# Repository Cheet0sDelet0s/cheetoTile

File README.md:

# cheetoTile
an attiny based rgb led tiling system

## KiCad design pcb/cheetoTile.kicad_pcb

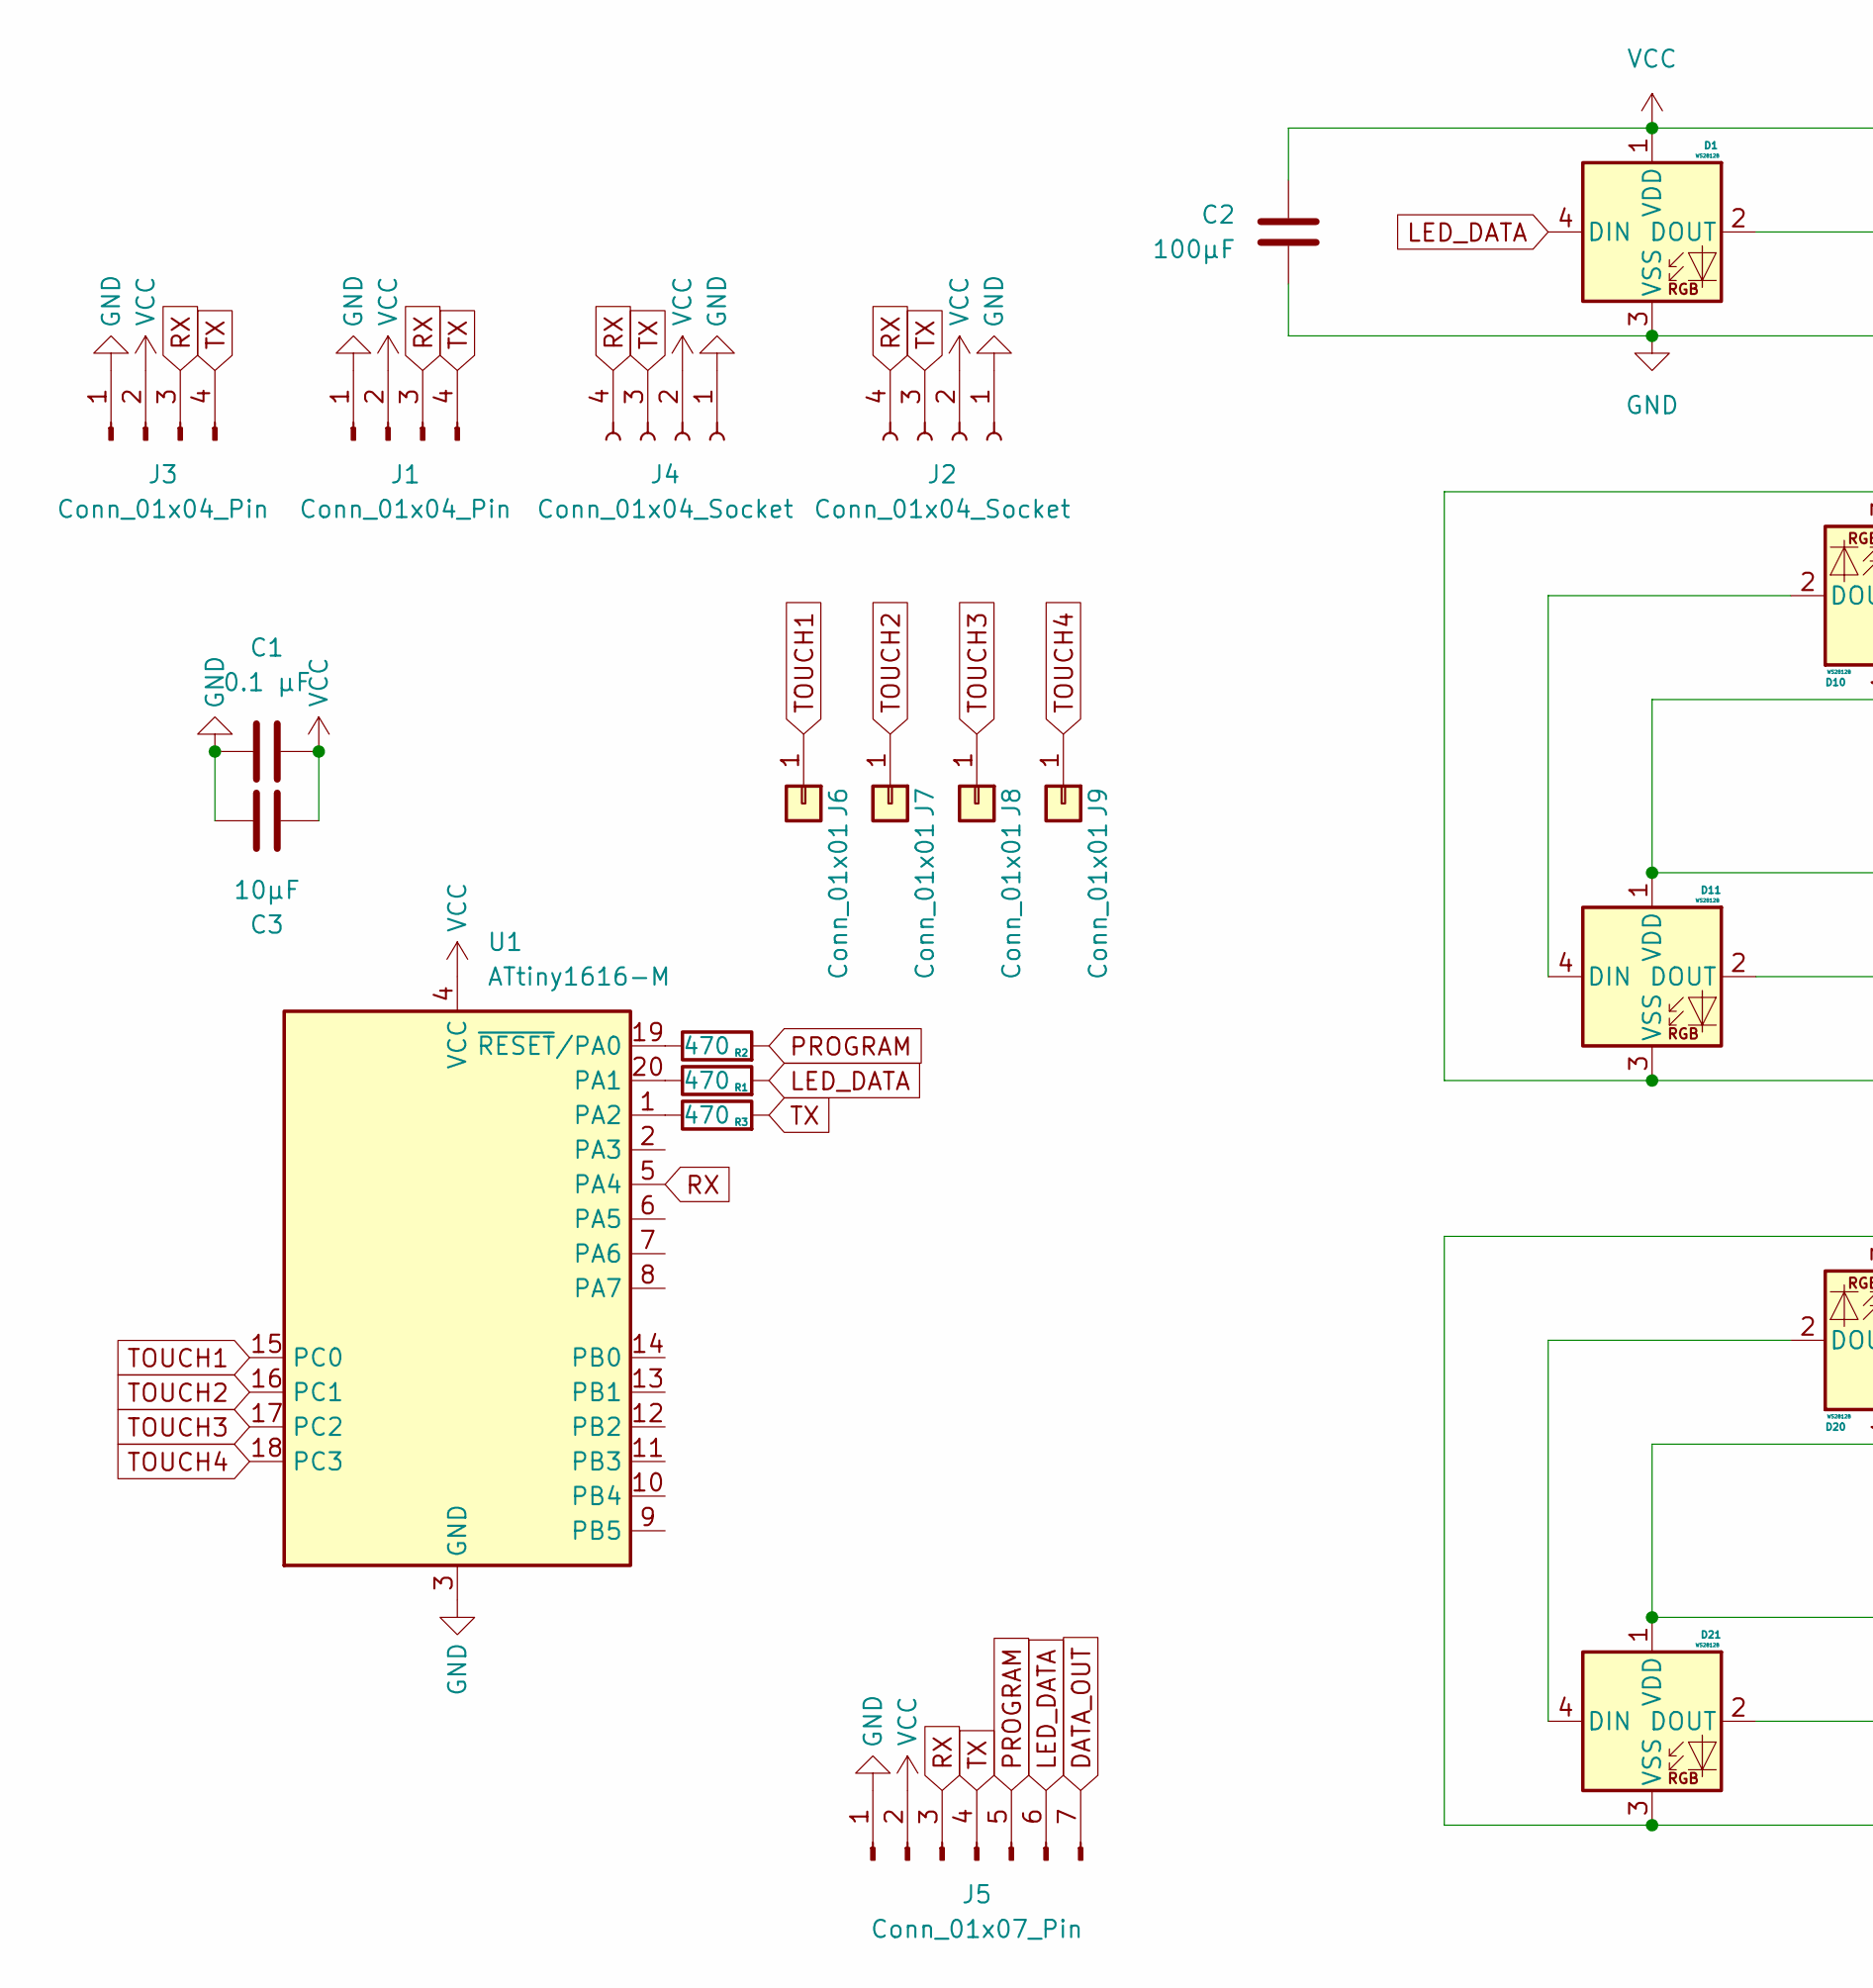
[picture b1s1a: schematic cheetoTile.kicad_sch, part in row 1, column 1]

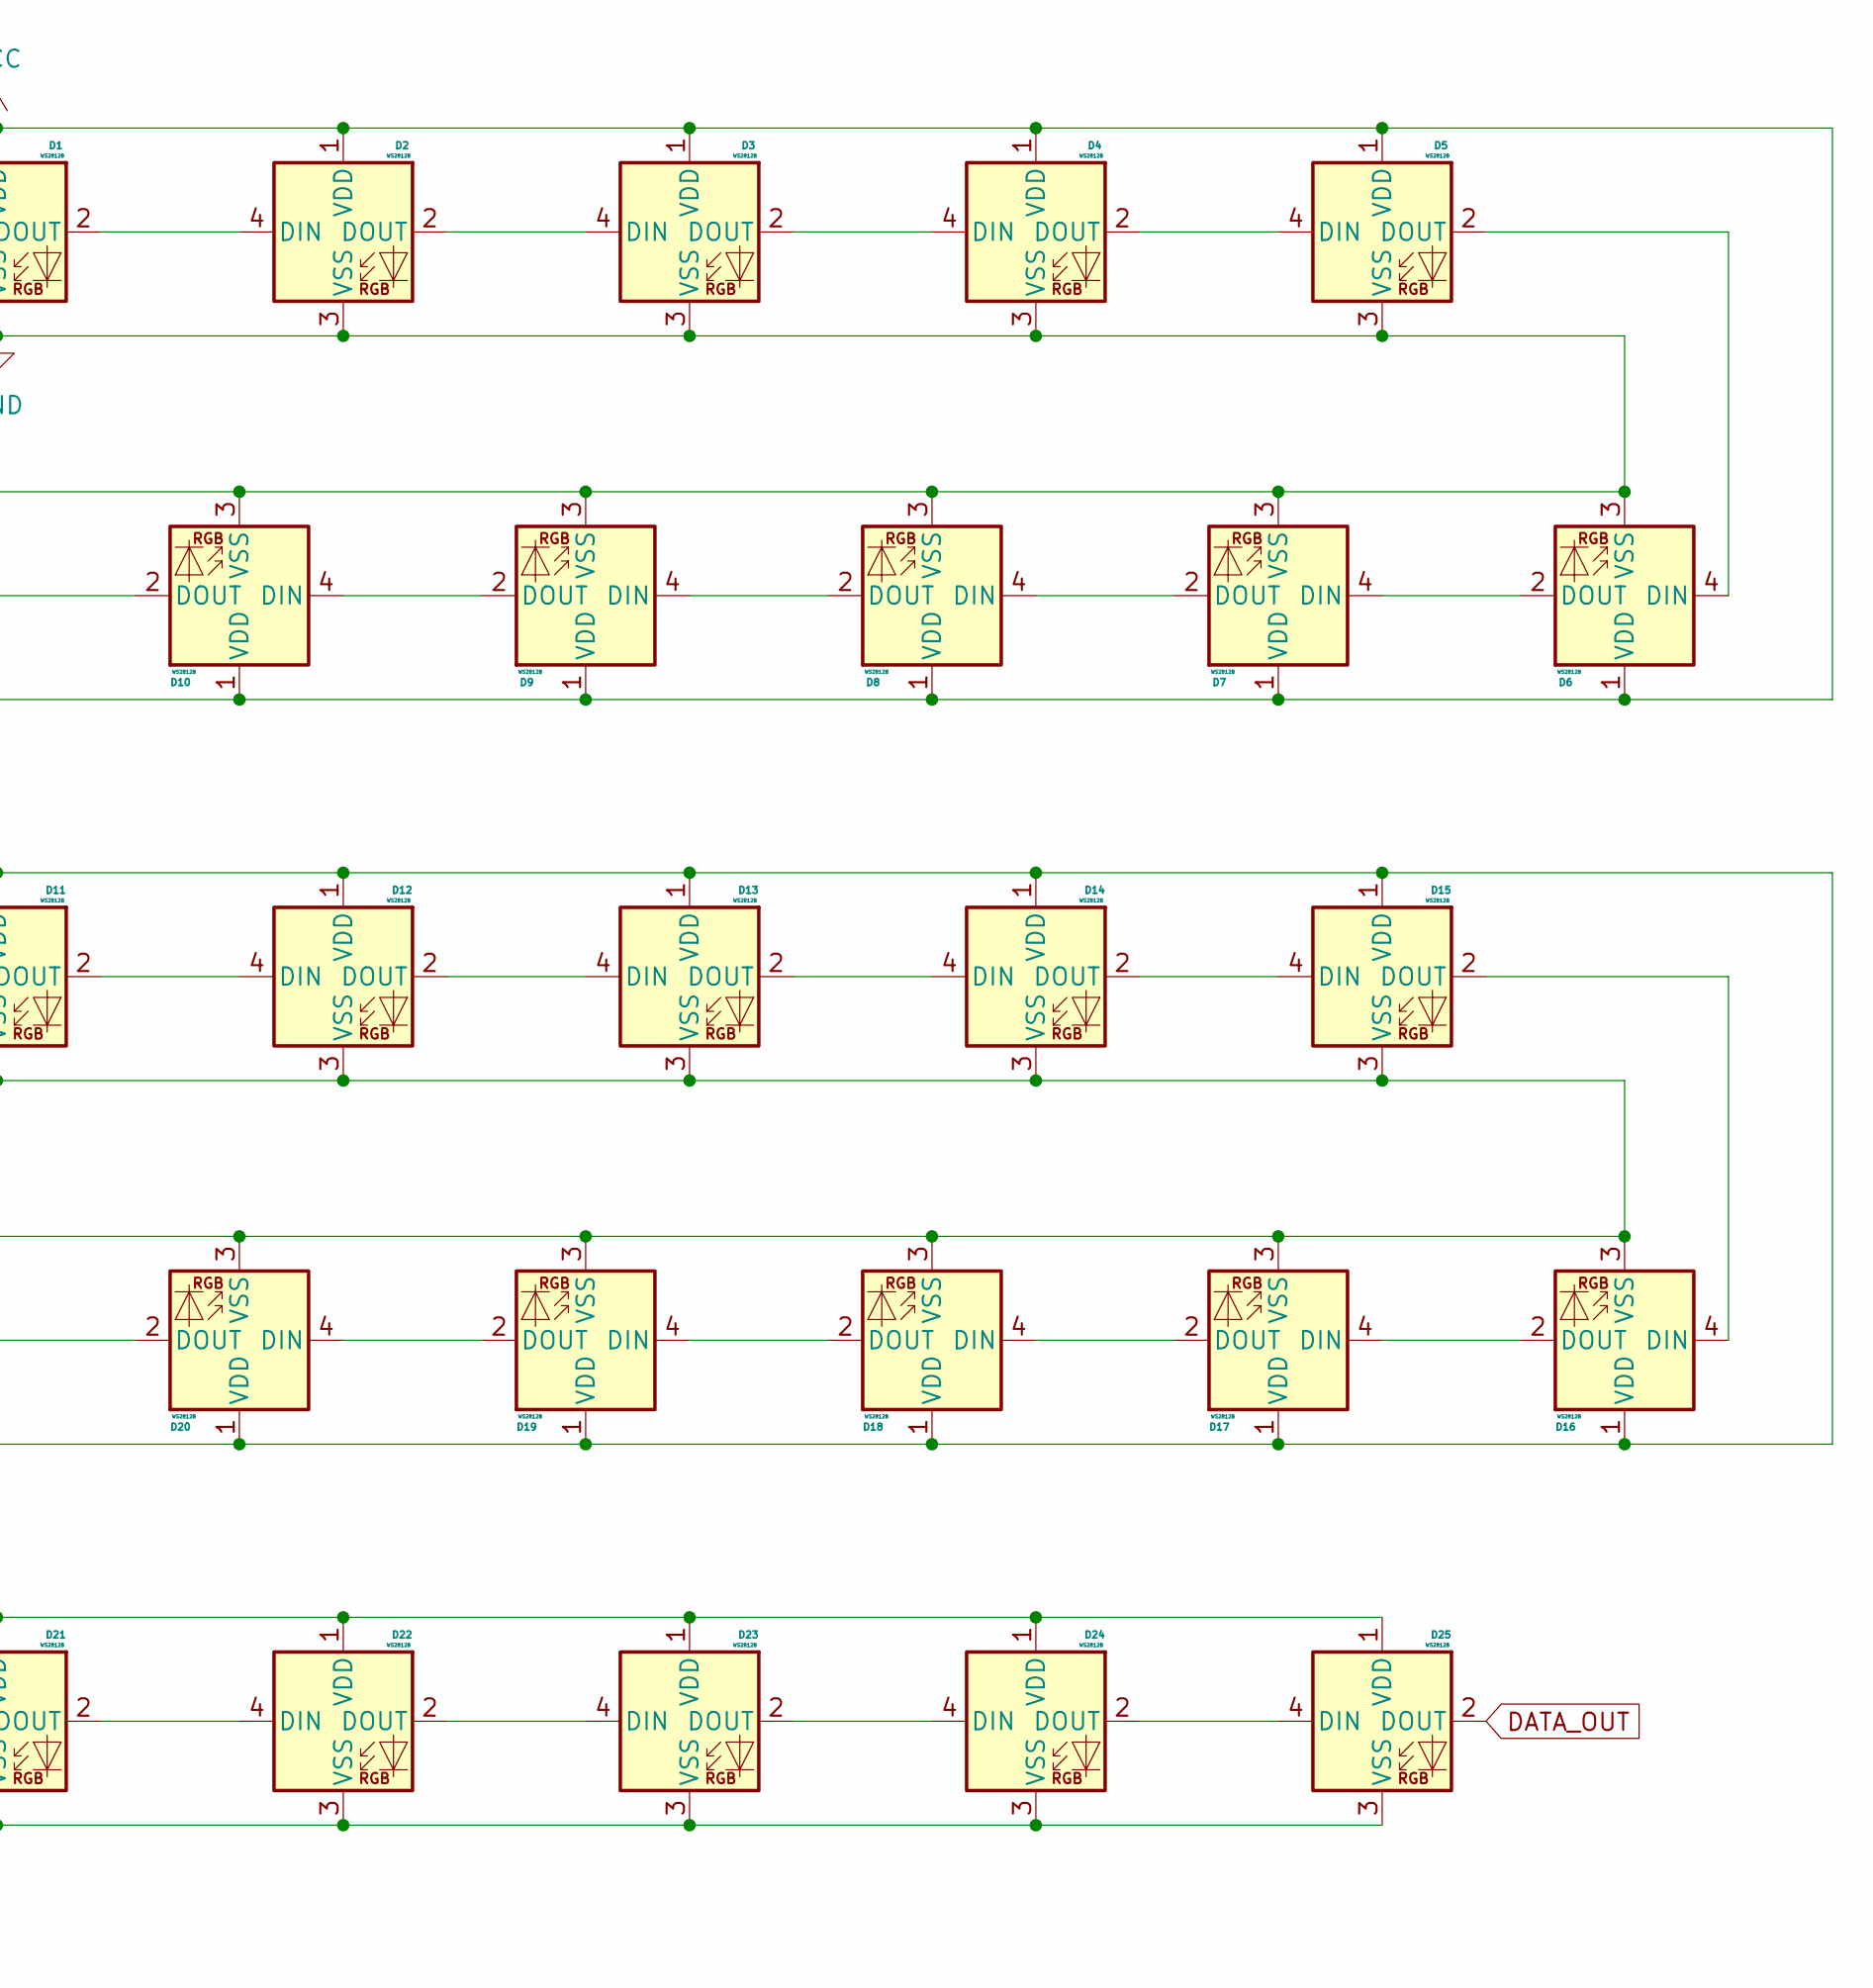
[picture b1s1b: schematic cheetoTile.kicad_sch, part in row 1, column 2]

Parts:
C1: 0.1 µF; C_0805_2012Metric_Pad1.18x1.45mm_HandSolder
C2: 100µF; C_1206_3216Metric_Pad1.33x1.80mm_HandSolder
C3: 10µF; C_0805_2012Metric_Pad1.18x1.45mm_HandSolder
D1, D2, D3, D4, D5, D6, D7, D8, D9, D10, D11, D12, D13, D14, D15, D16, D17, D18, D19, D20, D21, D22, D23, D24, D25: WS2812B; LED_WS2812B_PLCC4_5.0x5.0mm_P3.2mm
J1, J3: Conn_01x04_Pin; PinHeader_1x04_P2.54mm_Horizontal
J2, J4: Conn_01x04_Socket; PinHeader_1x04_P2.54mm_Horizontal
J5: Conn_01x07_Pin; PinHeader_1x07_P2.54mm_Vertical
J6, J7, J8, J9: Conn_01x01; TestPoint_Pad_1.0x1.0mm
R1, R2, R3: 470; C_0805_2012Metric_Pad1.18x1.45mm_HandSolder
U1: ATtiny1616-M; VQFN-20-1EP_3x3mm_P0.4mm_EP1.7x1.7mm

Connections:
DATA_OUT: D25.2 (DOUT), J5.7
GND: C1.1, C2.2, C3.1, D1.3 (VSS), D2.3 (VSS), D3.3 (VSS), D4.3 (VSS), D5.3 (VSS), D6.3 (VSS), D7.3 (VSS), D8.3 (VSS), D9.3 (VSS), D10.3 (VSS), D11.3 (VSS), D12.3 (VSS), D13.3 (VSS), D14.3 (VSS), D15.3 (VSS), D16.3 (VSS), D17.3 (VSS), D18.3 (VSS), D19.3 (VSS), D20.3 (VSS), D21.3 (VSS), D22.3 (VSS), D23.3 (VSS), D24.3 (VSS), D25.3 (VSS), J1.1, J2.1, J3.1, J4.1, J5.1, U1.3 (GND), U1.21 (GND)
LED_DATA: D1.4 (DIN), J5.6, R1.2
unnamed: D1.2 (DOUT), D2.4 (DIN)
unnamed: D2.2 (DOUT), D3.4 (DIN)
unnamed: D3.2 (DOUT), D4.4 (DIN)
unnamed: D4.2 (DOUT), D5.4 (DIN)
unnamed: D5.2 (DOUT), D6.4 (DIN)
unnamed: D6.2 (DOUT), D7.4 (DIN)
unnamed: D7.2 (DOUT), D8.4 (DIN)
unnamed: D8.2 (DOUT), D9.4 (DIN)
unnamed: D9.2 (DOUT), D10.4 (DIN)
unnamed: D10.2 (DOUT), D11.4 (DIN)
unnamed: D11.2 (DOUT), D12.4 (DIN)
unnamed: D12.2 (DOUT), D13.4 (DIN)
unnamed: D13.2 (DOUT), D14.4 (DIN)
unnamed: D14.2 (DOUT), D15.4 (DIN)
unnamed: D15.2 (DOUT), D16.4 (DIN)
unnamed: D16.2 (DOUT), D17.4 (DIN)
unnamed: D17.2 (DOUT), D18.4 (DIN)
unnamed: D18.2 (DOUT), D19.4 (DIN)
unnamed: D19.2 (DOUT), D20.4 (DIN)
unnamed: D20.2 (DOUT), D21.4 (DIN)
unnamed: D21.2 (DOUT), D22.4 (DIN)
unnamed: D22.2 (DOUT), D23.4 (DIN)
unnamed: D23.2 (DOUT), D24.4 (DIN)
unnamed: D24.2 (DOUT), D25.4 (DIN)
unnamed: R1.1, U1.20 (PA1)
unnamed: R3.1, U1.1 (PA2)
unnamed: R2.1, U1.19 (~RESET/PA0)
PROGRAM: J5.5, R2.2
RX: J1.3, J2.4, J3.3, J4.4, J5.3, U1.5 (PA4)
TOUCH1: J6.1, U1.15 (PC0)
TOUCH2: J7.1, U1.16 (PC1)
TOUCH3: J8.1, U1.17 (PC2)
TOUCH4: J9.1, U1.18 (PC3)
TX: J1.4, J2.3, J3.4, J4.3, J5.4, R3.2
VCC: C1.2, C2.1, C3.2, D1.1 (VDD), D2.1 (VDD), D3.1 (VDD), D4.1 (VDD), D5.1 (VDD), D6.1 (VDD), D7.1 (VDD), D8.1 (VDD), D9.1 (VDD), D10.1 (VDD), D11.1 (VDD), D12.1 (VDD), D13.1 (VDD), D14.1 (VDD), D15.1 (VDD), D16.1 (VDD), D17.1 (VDD), D18.1 (VDD), D19.1 (VDD), D20.1 (VDD), D21.1 (VDD), D22.1 (VDD), D23.1 (VDD), D24.1 (VDD), D25.1 (VDD), J1.2, J2.2, J3.2, J4.2, J5.2, U1.4 (VCC)

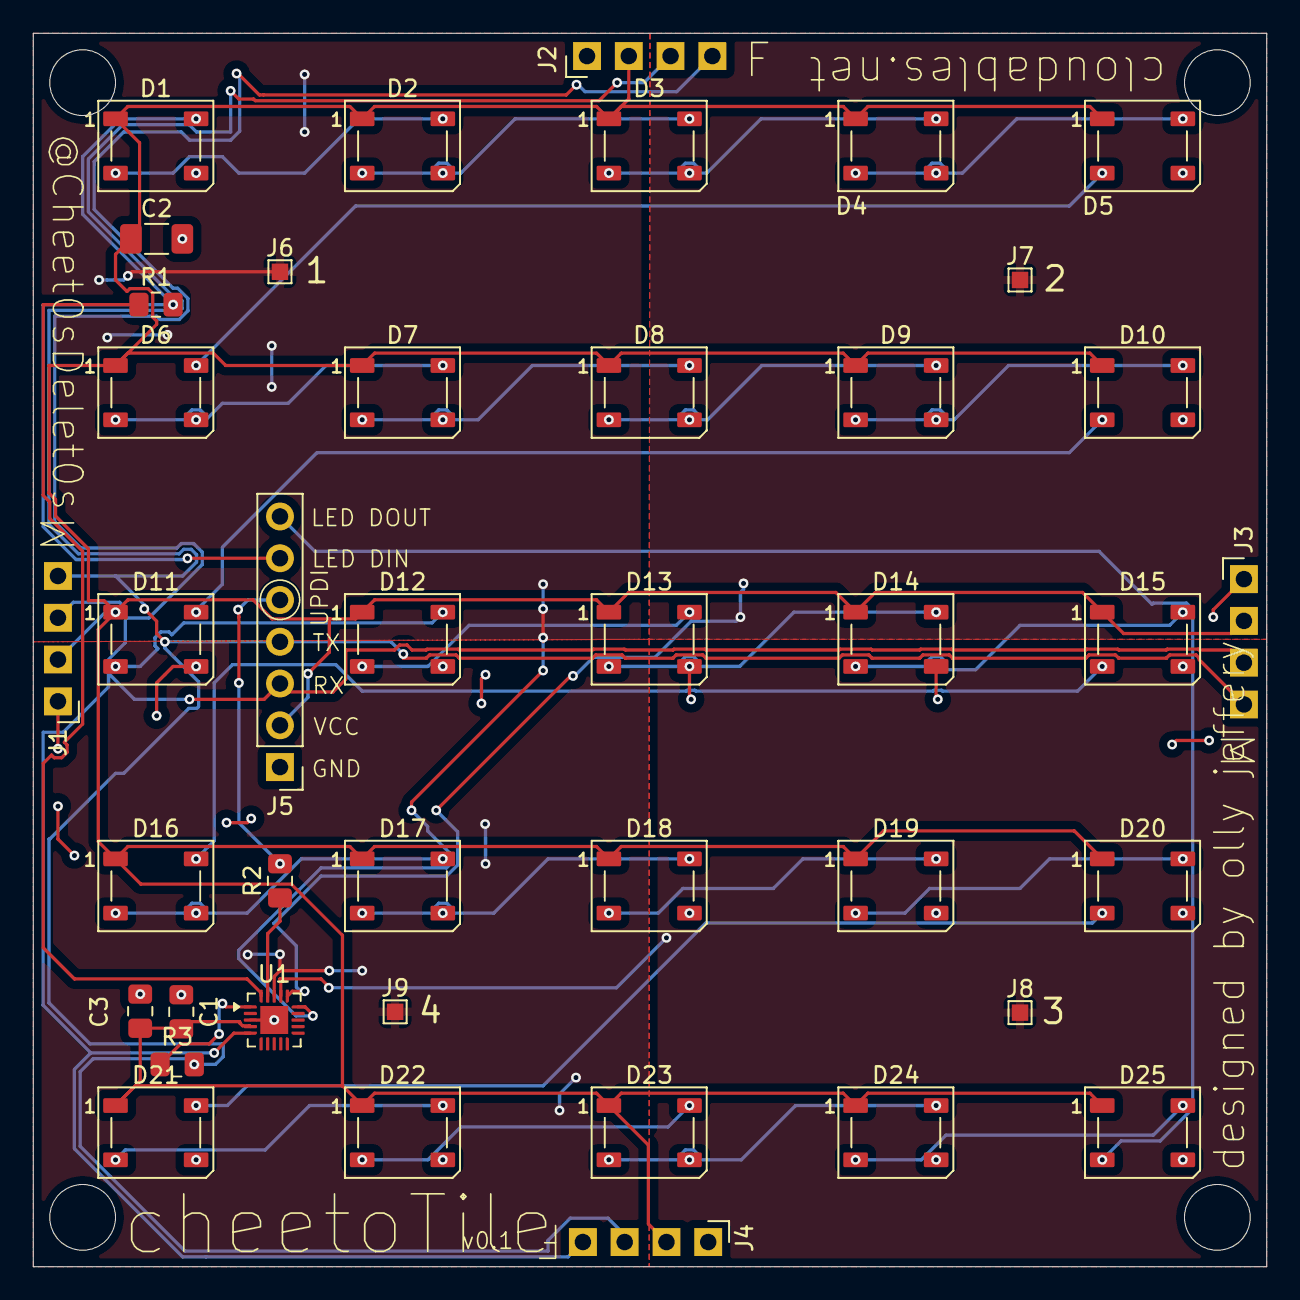
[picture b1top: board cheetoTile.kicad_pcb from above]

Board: 2 copper layers, 75.0 x 75.0 mm, 41 parts (0 on the bottom side), 38 nets.

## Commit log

2025-12-14 added pcb files
